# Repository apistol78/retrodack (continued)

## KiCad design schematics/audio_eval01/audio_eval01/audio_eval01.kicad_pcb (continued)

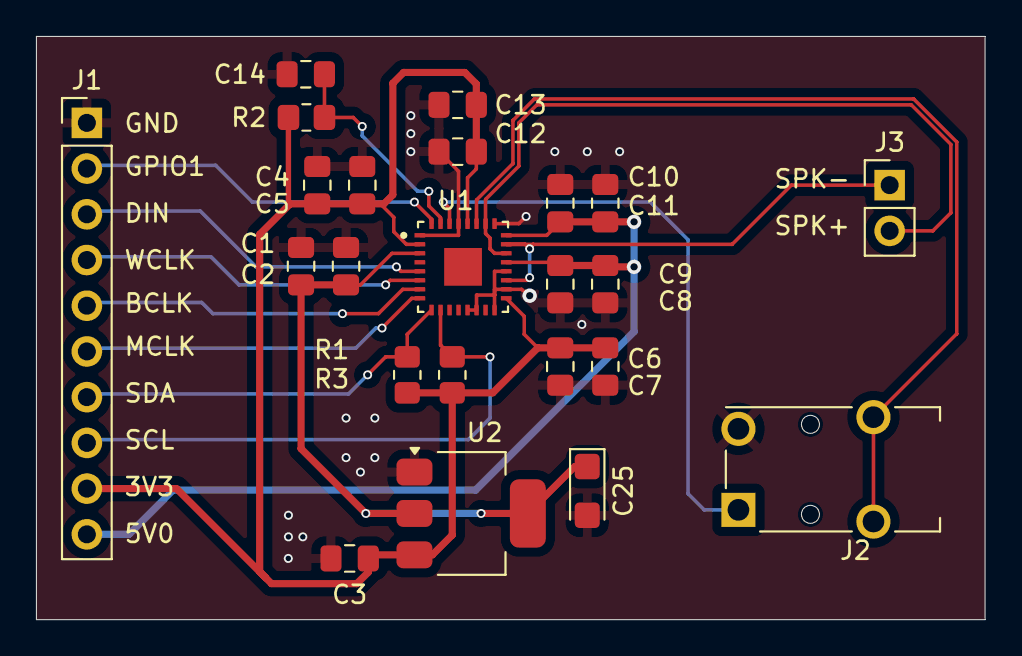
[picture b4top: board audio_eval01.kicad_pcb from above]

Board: 2 copper layers, 52.7 x 32.4 mm, 23 parts (0 on the bottom side), 16 nets.

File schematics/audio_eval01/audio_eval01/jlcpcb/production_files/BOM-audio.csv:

Comment,Designator,Footprint,LCSC,Quantity
22uF,"C11,C13,C2,C3,C5,C7,C9",C_0805_2012Metric_Pad1.18x1.45mm_HandSolder,C15850,7
4k7,"R1,R2,R3",R_0805_2012Metric_Pad1.20x1.40mm_HandSolder,C17673,3
~,U1,QFN50P500X500X100-33N,C2667049,1
0.1uF,"C1,C10,C12,C14,C4,C6,C8",C_0805_2012Metric_Pad1.18x1.45mm_HandSolder,C28233,7
AMS1117-1.8,U2,SOT-223-3_TabPin2,C6185,1
47uF,C25,CP_EIA-3216-18_Kemet-A,C7190,1
Conn_01x02_Pin,J3,PinHeader_1x02_P2.54mm_Vertical,,1
Conn_01x10_Pin,J1,PinHeader_1x10_P2.54mm_Vertical,,1
AudioJack3,J2,Jack_3.5mm_Switronic_ST-005-G_horizontal,,1

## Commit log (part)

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2025-05-09 Added initial parts document.
2025-05-11 A lot of work; beginning of mainboard schematics, SoC setup etc.
2025-05-12 Much work on mainboard.
2025-05-13 Built in UART in icesugar working, able to write from C++ to host.
2025-05-13 More mainboard schematics work.
2025-05-14 Proper placement of screen on PCB.
2025-05-15 Trace length tuned for LCD and SRAM. Also reduced size of board a bit.
2025-05-15 More work on mainboard schematic.
2025-05-16 SD card connector fixed in schematics. Added JLCPBC part numbers to some components.
2025-05-17 Audio evaluation PCB added
2025-05-18 Audio evaluation board work.
2025-05-20 Prepared Audio evaluation board for manufacture.
2025-05-21 Experiment with I2C and trackball device.
2025-05-21 Typo in Interrupt.c fixed.
2025-05-21 Added a link to suitable audio jack for the audio eval board.
2025-05-22 Updated solution files to be compatible with SB 4.0
2025-05-23 Able to build runtime and firmware using HAL from Klara-RV.
2025-05-23 Begun implementing support for automatically generate a FS image from folder in emulator.
2025-05-25 Mainboard work, trying to figure out optimal outline.
2025-05-25 Ensure to call crt_init in firmware so printf are working properly.
2025-05-26 Added video device to emulator. Begun work on Dashboard software.
2025-05-26 Updated usage of KlaraRV HAL library.
2025-05-26 Updated build script for Win64.
2025-05-26 Added demo from Rv32 to dashboard for profiling.
2025-05-27 Flat flex connector for interconnect.
2025-05-28 Added load switch to mainboard to control startup.
2025-05-29 Removed use of BRAM in SOC since SDRAM is now working.
2025-05-30 Updated Windows build scripts.
2025-05-31 Added (internal) SD card to system.
2025-06-01 Audio evaluation board tested with I2S device and SOC.
2025-06-02 Moved ELF loading into Runtime library.
2025-06-03 External SD pins updated; for testing using external PCB.
2025-06-03 Trying to get SD working on hw; need firmware to be able to boot into dashboard.
2025-06-04 Fixed loading of ELF from firmware.
2025-06-04 Able to use internal SD card connector on icesugar pro.
2025-06-04 Increased I$ and D$ on HW and verified on target.
2025-06-05 Added SPI Flash module for accessing on-board Flash for XIP execution of firmware.
2025-06-05 Image conversion script to generate a splash screen.
2025-06-05 Write firmware into flash and execute in place; verified on HW.
2025-06-07 Stubbed audio interrupt output on DAC GPIO pin.
2025-06-07 Able to initialize trackball and audio (same I2C bus) and play audio on HW.
2025-06-07 Launch tool rewritten, able to reset and upload binary without having running software pool serial. Audio sample moved into Dashboard.
2025-06-07 Increased D$ cache and made it combinatorial.
2025-06-07 Audio interrupt connected to SODIMM connector.
2025-06-09 Various cleanup. Also added VIDEO controller to RTL.
2025-06-12 Revision 1 of mainboard finished and ordered from JLCPCB.
2025-06-13 Incorrect part number and also incorrect footprint fixed. Another attempt at JLCPCB.
2025-06-16 Doom source.
2025-06-16 VS code configurations.
2025-06-16 Using (non working) emulator I2C device.
2025-06-16 Added iCESugar Pro documenation.
2025-06-16 Reverted back Dashboard main to be playing music.
2025-06-17 Firmware splash screen etc.
2025-06-17 Updated design rules for fpgaboard.
2025-06-18 Added ScummVM to solution.
2025-06-18 Running emulator SOC in a separate thread.
2025-06-18 Added trackball device to I2C bus in emulator.
2025-06-30 Actual mainboard hardware work; display, vram, audio, sd card etc.
2025-07-01 CPU bus mux not registered.
2025-07-01 Sorting indexed pins before generating top IO.
2025-07-03 HW pins and top level setup. Verified GPIO extender and GPIO interrupt.
2025-07-03 More work on buttboard.
2025-07-03 Added control buttons to buttboard; adjusted cutout.
2025-07-03 Implemented a simple caching scheme for SD reading.
2025-07-09 Attempt to send line multiple times before failing.
2025-07-13 Button board ordered from JLCPCB.
2025-07-13 Reset timer wall time when runtime is initialized.
2025-07-19 Mul and div working on HW.
2025-07-21 Input on HW working.
2025-07-22 Ported console from RV to runtime.
2025-07-29 Added debug drawing of video in firmware so we can fix video controller timing.
2025-08-01 Revert "Added debug drawing of video in firmware so we can fix video controller timing."
    This reverts commit 0c270e1258039841cf61a44d37201311bf6f4210.
2025-08-01 Revert "Updated VIDEO_controller instance in RD top module."
    This reverts commit b516cc524e68dd1070d07c6e6fa24eb520875736.
2025-08-02 Input in ScrummRV. Able to set TB color from app. Firmware loads "BOOT" executable.
2025-08-05 Updated audio device.
2025-08-05 ModPlayer playing in stereo.
2025-08-05 Enabled improved kernel scheduling.
2025-08-06 Added the console to firmware.
2025-08-08 Using DualPort instead of CPU_BusMux.
2025-08-08 Reverted back UART speed.
2025-08-08 Using XBAR for interconnect, not verified on HW.
2025-08-09 XBAR working on HW.
2025-08-09 Using DMA device; not verified on HW.
2025-08-10 More optimizations in RT video using DMA.
2025-08-10 Added aspect layout to emulator view so we always ensure proper aspect ratio.
2025-08-12 Added SD CARD signal to SD module.
2025-08-12 Do not attempt to initialize file system if no SD card inserted.
2025-08-14 A lot of minor fixes; most notably DMA and Audio.
2025-08-14 Some tweaks to runtime and firmware.
2025-08-15 SDL 2 shim project.
2025-08-18 Bring in symbols from RT CRT even of "gc sections" are used when linking; need linker script to be used.
2025-08-19 Using 32-bit video mode in SDL.
2025-08-20 Filter of trackball input deltas.
2025-08-21 Cleanup function names in kernel.
2025-08-24 Updated emulator with changes to GDB server.
2025-08-25 Able to debug emulated applications from VSCode.
2025-08-25 GDB server as a device to receive ticks from CPU.
2025-08-26 File system image is now recursive.
2025-08-27 Creating firmware binary in build script again.
2025-08-30 Minor cleanup in build script.
2025-09-09 Revert "Firmware updates, able to communicate through UART without explicitly going into "remote" mode."
    This reverts commit 9727644ebab89752526659782f05a817340735c4.
2025-09-09 Fixed PLL configuration.
2025-09-09 Keep logs from yosys and nextpnr in build folder. Added memory test to firmware. Silenced warnings in top module.
2025-09-10 ScummVM able to read it's config file.
2025-09-10 Fixed incorrect address mapping to AUDIO_controller.
2025-09-11 Added VIDEO_sprite module to top.
2025-09-11 CPU access to sprite manager.
2025-09-12 Added unknown device as sprite device in emulator.
2025-09-12 Build script cleanup. Adjusted Sprite interface.
2025-09-12 Warp mouse position in input. Set hot spot of mouse cursor. Replaced SW cursor with HW cursor in ScummRV.
2025-09-14 Using I2C_v2 module, probably not working.
2025-09-15 Added status bar to emulator.
2025-09-20 Using new I2C device, updated runtime accordingly. Works on HW.
2025-09-21 Added another DMA channel, channel 0 used by audio and 1 used by video.
2025-09-21 Fixed race issue with enter/leave critical region in kernel.
2025-09-21 Added "simon" engine to ScummRV.
2025-09-22 Added the Sprite device to emulator.
2025-10-02 USB device mass storage device; need firmware refactorization.
2025-10-06 Added PLL generation script for TLV320DAC setup.
2025-10-12 Improved error recovery when sending data to target through UART.
2025-10-19 SignalView widget added to Emulator to show interrupt signals.
2025-10-21 Using larger sprites. Also create yosys script used to synth.
2025-10-21 Do not save FP registers since we're using Zfinx extension now.
2025-10-22 Fixed incorrect string compare defines in ScummRV.
2025-10-23 Implemented _gettimeofday in CRT. Various fixes and improvements.
2025-10-23 Updated emulator due to GDB server changes.
2025-10-25 Added LVGL 3rdp project. Initial experiment in Dashboard.
2025-10-26 More work on mainboard, mostly done but need double checking.
2025-10-26 Slikscreen fixes.
2025-10-28 Minor tweaks to mainboard, 1 mm narrower at the widest position allow for proper on/off switch. Double checked the phone jack connections.
2025-10-30 Added a NES emulator, based on SimpleNES but heavily modified and optimized.
2025-11-02 Various improvments to emulator and apps. Using new HAL DMA.
2025-11-02 Mainboard PCB work, moved debug header down a bit and mapped JLCPCB parts.
2025-11-02 Logging some signals in VCD trace.
2025-11-02 Begun wiring up BLE/BHE from SRAM to FPGA on mainboard.
2025-11-03 Using write mask in top level module.
2025-11-04 Prepared RD top module for video wmask.
2025-11-06 Stubbed PCX loading in Graphics.
2025-11-06 Stepping in emulator.
2025-11-07 Wired up BLE/BHE pins of the video SRAM on mainboard.
2025-11-11 Increased size of data cache on HW.
2025-11-11 Removed Doom from solution.
2025-11-17 Replaced ADC with a proper "Fuel Gauge" on mainboard.
2025-11-17 Some updates on netclasses.
2025-11-19 Some minor cleanups in mainboard.
2025-11-19 Added some parts to JLCPCB BOM.
2025-11-23 Added CPU_BranchPrediction to build script.
2025-12-02 Build script check firmware hash to prevent redundant flashing of target.
2025-12-04 Some minor cleanup in emulator.
2025-12-08 Automatically setup terminal with tool paths.
2025-12-10 Able to reset signal. Video ensure to wait on next vblank.
2025-12-11 Rev 2 pin constraints. Battery and RTC support.
2025-12-12 Updated DMA device mapping in emulator.
2025-12-21 Reverted DMA re-factorizations; using to simpler DMA modules again due to logic utilization.
2025-12-25 Added functions to play mono samples through HAL audio.
2025-12-25 Updated audio runtime and emulator.
2025-12-30 Slightly simpler device mapping in Emulator.
2026-01-02 Audio fixes, new system works as designed. Investigated input issues and fixed stuck keys. Able to use HW SD read path.
2026-01-03 Work on custom FPGA board with more RAM and beefier FPGA.
2026-01-04 Added Tetris project. Overall cleanup of runtime.
2026-01-05 Some work on FPGA board, adding some decoupling, SODIMM signals etc.
2026-01-06 FPGA board update; using 6 layer setup and "via in pad".
2026-01-06 Drawing score in Tetris.
2026-01-07 Added more drawing commands to Graphics. Minor cleanup in Tetris.
2026-01-07 More work on FPGA board.
2026-01-08 Added "fuel gauge" I2C device to emulator. Moved cursor bitmap into Runtime. Added battery charge indicator to console.
2026-01-08 Top row of SODIMM wired up to FPGA in fpga board.
2026-01-09 Refactored emulator; now with UI and emulator separated properly.
2026-01-10 Acquire/release I2C access.
2026-01-11 Added register view to emulator.
2026-01-12 Some work on FPGA board.
2026-01-12 SODIMM connector fully wired up to FPGA.
2026-01-14 Fixed 3rdp update script.
2026-01-15 Show proper register names in the emulator.
2026-01-15 Removed auto detect tasks.
2026-01-20 Using graphics to draw console.
2026-01-24 Reading kernel data from emulator to visualize kernel threads.
2026-01-25 Adjusted Emulator setup.
2026-02-12 HW stable again, a lot of debugging hooks added. Exposed a lot of registers and CPU stats through JTAG connection.
2026-02-14 Re-enabled D$ WB.
2026-02-15 Begun implementing app selector in firmware.
2026-02-16 Some minor work on new app selector.
2026-02-17 Firmware work, mostly working but need a cleanup pass.
2026-02-17 New background in launcher; also some minor animation.
2026-02-18 Clean up in launcher firmware.
2026-02-18 Masked icons in launcher. Ensure SD card is reset when soft restart system.
2026-02-20 Lots of fixes; cold reset when writing to ffff_ffff, firmware updates, I2C fixed, reverted changes in ScummRV audio etc.
2026-02-21 Enabled WB on CPU.
